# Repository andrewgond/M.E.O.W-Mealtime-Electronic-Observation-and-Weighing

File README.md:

---

# M.E.O.W. — Mealtime Electronic Observation & Weighing (WIP)

**An Open-Source Smart Pet Feeder with Integrated Weight Tracking**
*Senior Design Capstone — Oregon State University*
*Andrew Gondoputro
*Ahmad Alajmi
*Craig Kelley

---

## Project Status: Work in Progress (WIP)

This repository documents the development of the **M.E.O.W. automated pet feeder**, a system that dispenses food and logs pet weight using load cells and RFID identification. The goal is to support long-term tracking of pet health trends such as obesity, malnutrition, or abnormal feeding behavior.

---

# Overview

The M.E.O.W. system is designed to:

* Run on standard wall power
* Measure pet weight within ±20 grams
* Dispense food within ±60 grams
* Log food and weight data within 10 seconds
* Store at least 10 days of logs
* Support up to 4 pets via RFID
* Allow user-configurable feeding parameters

Unlike typical auto-feeders, M.E.O.W. integrates *health-relevant data logging* for improved wellness monitoring.

---

# DEI Commitment

The project emphasizes accessibility, inclusion, and open-source availability.
The system aims to be easy to use for any pet owner, with a simple UI and customizable configuration.

---

# System Architecture

## Top-Level Summary

The system is divided into modular subsystems:

* Power Distribution
* Enclosure & Kinematics
* Sensors
* Code & Database Storage
* Microcontroller (ESP32)
* UI + Web App

---

# 🔌 Block Diagram (Placeholder)

```
[ Block Diagram Placeholder — MEOW System ]
```

```
[ System-Level Diagram Placeholder — Showing Subsystem Connections ]
```

---

# 🔧 Subsystem Descriptions

### 1. Power Distribution

Converts AC wall power into stable low-voltage DC rails for sensors, logic, and actuators.

### 2. Enclosure & Kinematics

Includes the physical enclosure, motors, dispensing components, and protective mechanical structures.

### 3. Sensors

* Load cells to capture weight
* RFID reader for pet identification

### 4. Code & Database

MicroSD-based data storage for logs, timestamps, food dispensing events, and per-pet data.

### 5. Microcontroller

ESP32 manages sensors, actuator control, data logging, and UI communication.

### 6. UI + Web App

Browser-based dashboard for monitoring weight trends, adjusting feeding schedules, and visualizing logs.

---

# Interface Definitions

| Interface           | Description                          |
| ------------------- | ------------------------------------ |
| AC_pwr_in           | Wall power input                     |
| DC_pwr_in_5v        | Regulated 5V power rail              |
| env_weight          | Load cell weight signal              |
| env_rfid_dist       | RFID read distance                   |
| if_user_commands_in | User command interface               |
| motor_ctrl_out      | Motor control signals                |
| ui_disp_ui          | Display output                       |
| db_data_out         | Data sent from database              |
| db_data_to_ui       | Data sent from microcontroller to UI |

---

# Verification Framework

Each subsystem will include:

* Interface validation
* General validation
* Verification steps
* References
* Success criteria

Example tasks include:

* Maximum current draw calculations
* Logic level matching (ESP32 ↔ SD card)
* Regulator thermal margins
* Sensor precision/accuracy tests

---

# References

A `/docs/references.md` file will be added containing:

* Component datasheets
* Industry standards
* Research sources for pet feeding and behavior
* Market analysis references

---

# Future Work

### Technical Recommendations (WIP)

* Improve sensor calibration algorithms
* Add multi-pet discrimination logic
* Enhance UI accessibility
* Expand SD logging features
* Improve enclosure materials

### Teamwork/Communication Recommendations

* Better task delegation strategy
* Implement weekly fixed-scope sprints

---

# Project Roadmap

### Phase 1 — Hardware Bring-Up

* [ ] Power subsystem validation
* [ ] Load cell calibration
* [ ] Servo/stepper testing
* [ ] RFID module bring-up

### Phase 2 — Firmware

* [ ] Sensor polling loops
* [ ] SD logging system
* [ ] Motor control logic
* [ ] Error handling

### Phase 3 — UI + Data

* [ ] Web dashboard
* [ ] Trend graphs
* [ ] Pet profiles

### Phase 4 — Final Integration

* [ ] Full hardware + firmware integration
* [ ] Enclosure finalization
* [ ] Stress testing
* [ ] Final documentation

---

# Contact

Project Contributors:

* Ahmad Alajmi
* Andrew Gondoputro
* Craig Kelley

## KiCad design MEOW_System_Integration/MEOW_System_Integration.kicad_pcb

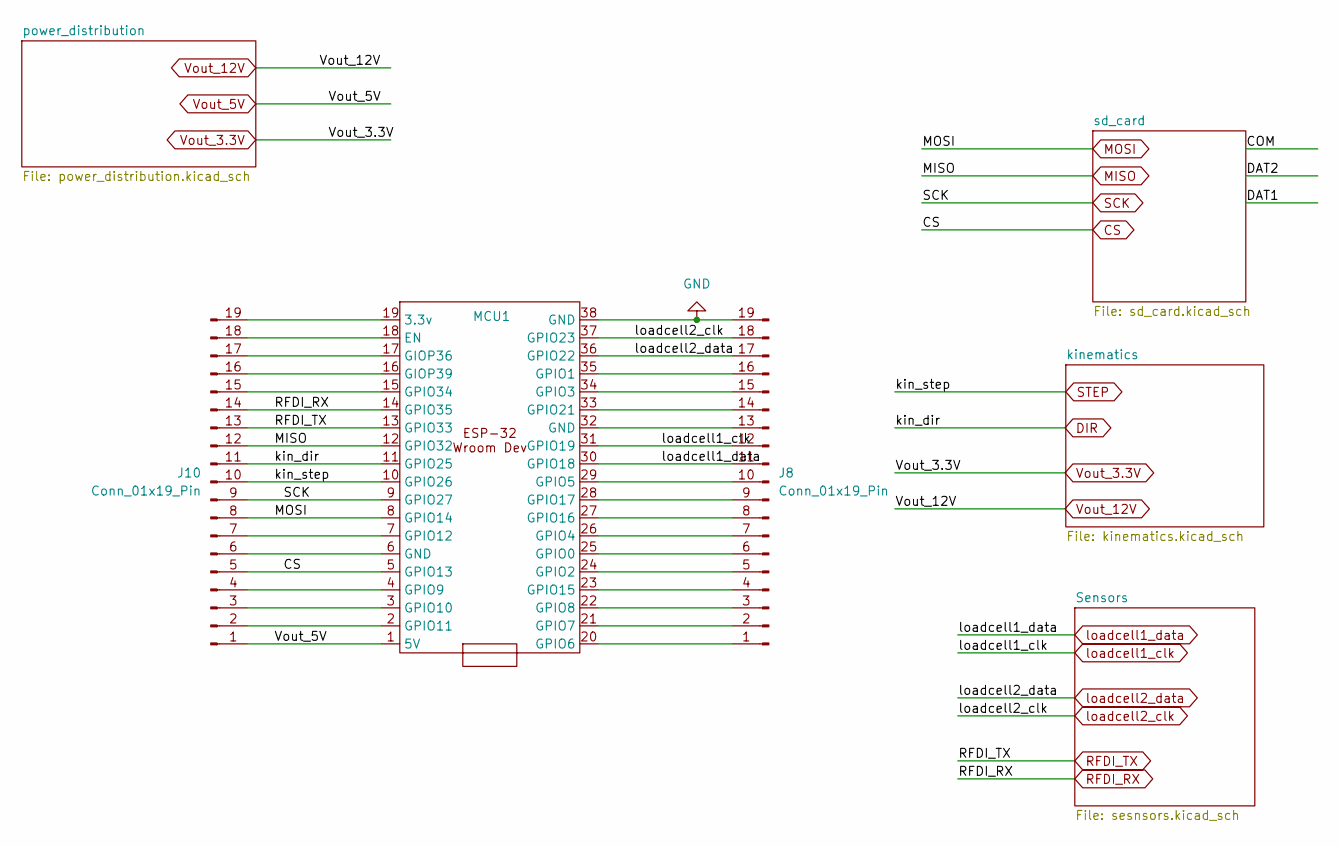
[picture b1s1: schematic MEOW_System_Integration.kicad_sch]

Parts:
J8, J10: Conn_01x19_Pin; PinHeader_1x19_P2.54mm_Vertical
MCU1: ESP32_38pin

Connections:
CS: J10.5, MCU1.5 (GPIO13); also elsewhere on the board
DIR: J10.11, MCU1.11 (GPIO25); also elsewhere on the board
GND: J8.19, MCU1.38 (GND); also elsewhere on the board
MISO: J10.12, MCU1.12 (GPIO32); also elsewhere on the board
MOSI: J10.8, MCU1.8 (GPIO14); also elsewhere on the board
unnamed: J8.1, MCU1.20 (GPIO6)
unnamed: J8.2, MCU1.21 (GPIO7)
unnamed: J8.3, MCU1.22 (GPIO8)
unnamed: J8.4, MCU1.23 (GPIO15)
unnamed: J8.5, MCU1.24 (GPIO2)
unnamed: J8.6, MCU1.25 (GPIO0)
unnamed: J8.7, MCU1.26 (GPIO4)
unnamed: J8.8, MCU1.27 (GPIO16)
unnamed: J8.9, MCU1.28 (GPIO17)
unnamed: J8.10, MCU1.29 (GPIO5)
unnamed: J8.13, MCU1.32 (GND)
unnamed: J8.14, MCU1.33 (GPIO21)
unnamed: J8.15, MCU1.34 (GPIO3)
unnamed: J8.16, MCU1.35 (GPIO1)
unnamed: J10.2, MCU1.2 (GPIO11)
unnamed: J10.3, MCU1.3 (GPIO10)
unnamed: J10.4, MCU1.4 (GPIO9)
unnamed: J10.6, MCU1.6 (GND)
unnamed: J10.7, MCU1.7 (GPIO12)
unnamed: J10.15, MCU1.15 (GPIO34)
unnamed: J10.16, MCU1.16 (GIOP39)
unnamed: J10.17, MCU1.17 (GIOP36)
unnamed: J10.18, MCU1.18 (EN)
unnamed: J10.19, MCU1.19 (3.3v)
RFDI_RX: J10.14, MCU1.14 (GPIO35); also elsewhere on the board
RFDI_TX: J10.13, MCU1.13 (GPIO33); also elsewhere on the board
SCK: J10.9, MCU1.9 (GPIO27); also elsewhere on the board
STEP: J10.10, MCU1.10 (GPIO26); also elsewhere on the board
Vout_5V: J10.1, MCU1.1 (5V); also elsewhere on the board
loadcell1_clk: J8.12, MCU1.31 (GPIO19); also elsewhere on the board
loadcell1_data: J8.11, MCU1.30 (GPIO18); also elsewhere on the board
loadcell2_clk: J8.18, MCU1.37 (GPIO23); also elsewhere on the board
loadcell2_data: J8.17, MCU1.36 (GPIO22); also elsewhere on the board

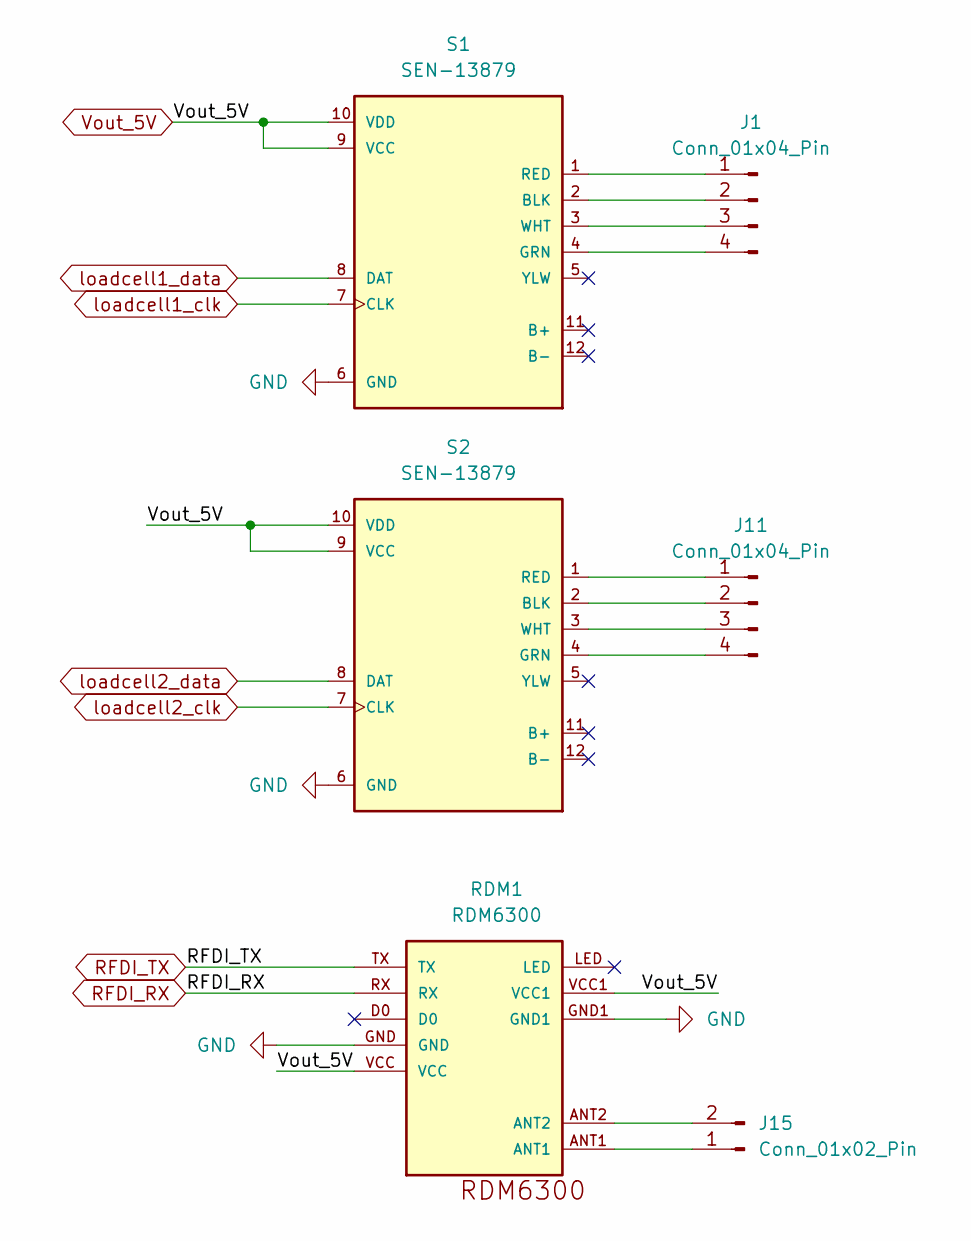
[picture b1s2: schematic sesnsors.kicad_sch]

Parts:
J1, J11: Conn_01x04_Pin; PinHeader_1x04_P2.54mm_Vertical
J15: Conn_01x02_Pin; PinSocket_1x02_P2.54mm_Vertical
RDM1: RDM6300
S1, S2: SEN-13879; SPARKFUN_SEN-13879

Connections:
GND: RDM1.GND, RDM1.GND1, S1.6 (GND), S2.6 (GND); also elsewhere on the board
unnamed: J1.1, S1.1 (RED)
unnamed: J1.2, S1.2 (BLK)
unnamed: J1.3, S1.3 (WHT)
unnamed: J1.4, S1.4 (GRN)
unnamed: J11.1, S2.1 (RED)
unnamed: J11.2, S2.2 (BLK)
unnamed: J11.3, S2.3 (WHT)
unnamed: J11.4, S2.4 (GRN)
unnamed: J15.1, RDM1.ANT1
unnamed: J15.2, RDM1.ANT2
RFDI_RX: RDM1.RX; also elsewhere on the board
RFDI_TX: RDM1.TX; also elsewhere on the board
Vout_5V: RDM1.VCC, RDM1.VCC1, S1.9 (VCC), S1.10 (VDD), S2.9 (VCC), S2.10 (VDD); also elsewhere on the board
loadcell1_clk: S1.7 (CLK); also elsewhere on the board
loadcell1_data: S1.8 (DAT); also elsewhere on the board
loadcell2_clk: S2.7 (CLK); also elsewhere on the board
loadcell2_data: S2.8 (DAT); also elsewhere on the board

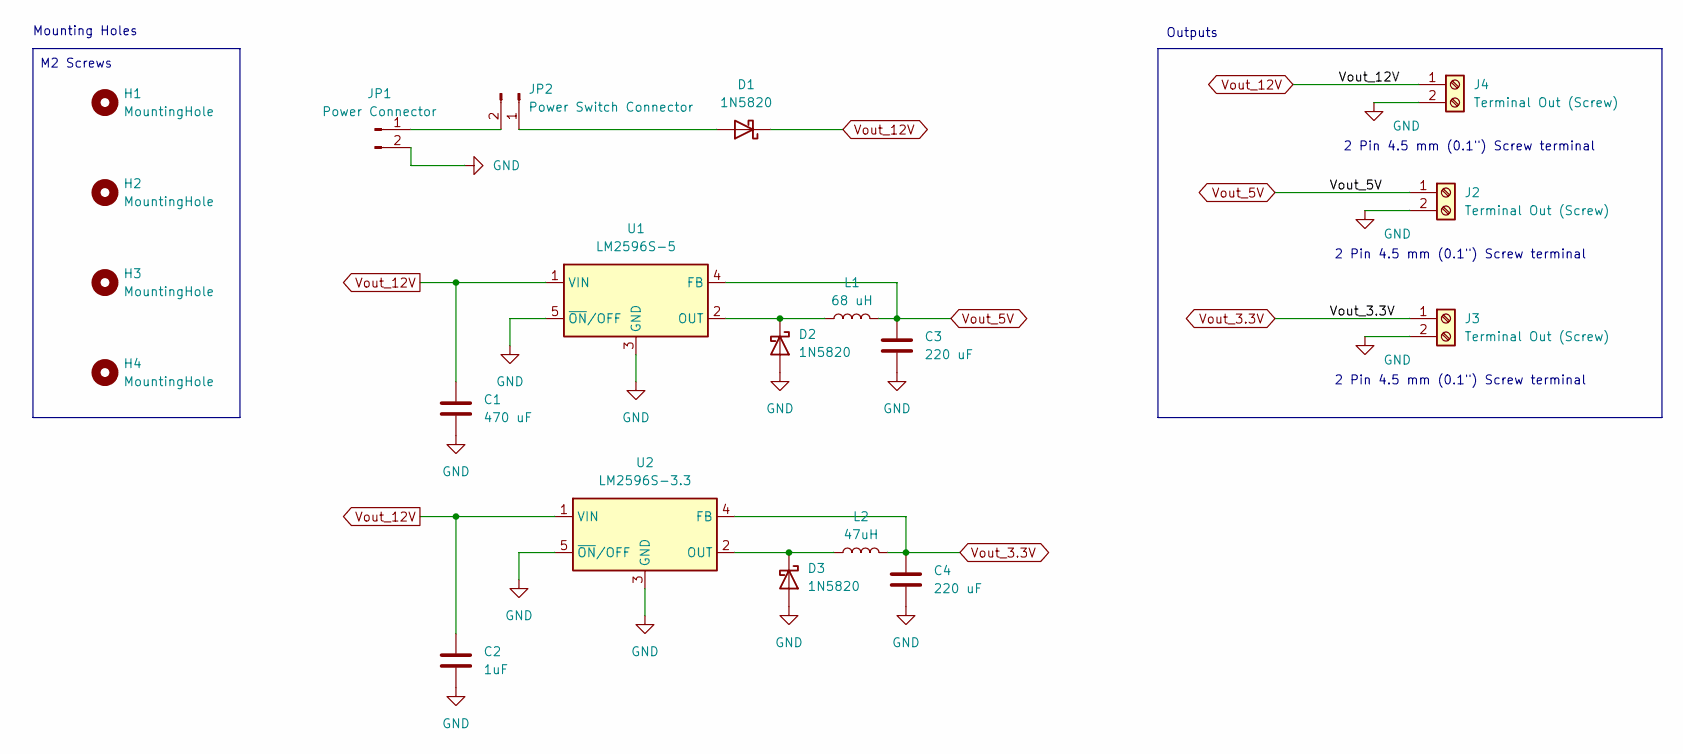
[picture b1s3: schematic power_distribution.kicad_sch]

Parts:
C1: 470 uF; CP_Elec_8x10
C2: 1uF; C_0603_1608Metric
C3, C4: 220 uF; CP_Elec_6.3x7.7
D1, D2, D3: 1N5820; D_SMA
H1, H2, H3, H4: MountingHole; MountingHole_3mm
J2, J3, J4: Terminal Out (Screw); TerminalBlock_TE_282834-2_1x02_P2.54mm_Horizontal
JP1: Power Connector; JST_EH_B2B-EH-A_1x02_P2.50mm_Vertical
JP2: Power Switch Connector; JST_EH_B2B-EH-A_1x02_P2.50mm_Vertical
L1: 68 uH; L_12x12mm_H4.5mm
L2: 47uH; L_12x12mm_H4.5mm
U1: LM2596S-5; TO-263-5_TabPin3
U2: LM2596S-3.3; TO-263-5_TabPin3

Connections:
GND: C1.2, C2.2, C3.2, C4.2, D2.2 (A), D3.2 (A), JP1.2, U1.3 (GND), U1.5 (~ON/OFF), U2.3 (GND), U2.5 (~ON/OFF); also elsewhere on the board
unnamed: D1.2 (A), JP2.1
unnamed: D2.1 (K), L1.1, U1.2 (OUT)
unnamed: D3.1 (K), L2.1, U2.2 (OUT)
unnamed: JP1.1, JP2.2
Vout_3.3V: C4.1, L2.2, U2.4 (FB); also elsewhere on the board
Vout_5V: C3.1, L1.2, U1.4 (FB); also elsewhere on the board
Vout_12V: C1.1, C2.1, D1.1 (K), U1.1 (VIN), U2.1 (VIN); also elsewhere on the board

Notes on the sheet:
Outputs
2 Pin 4.5 mm (0.1") Screw terminal
Mounting Holes
M2 Screws

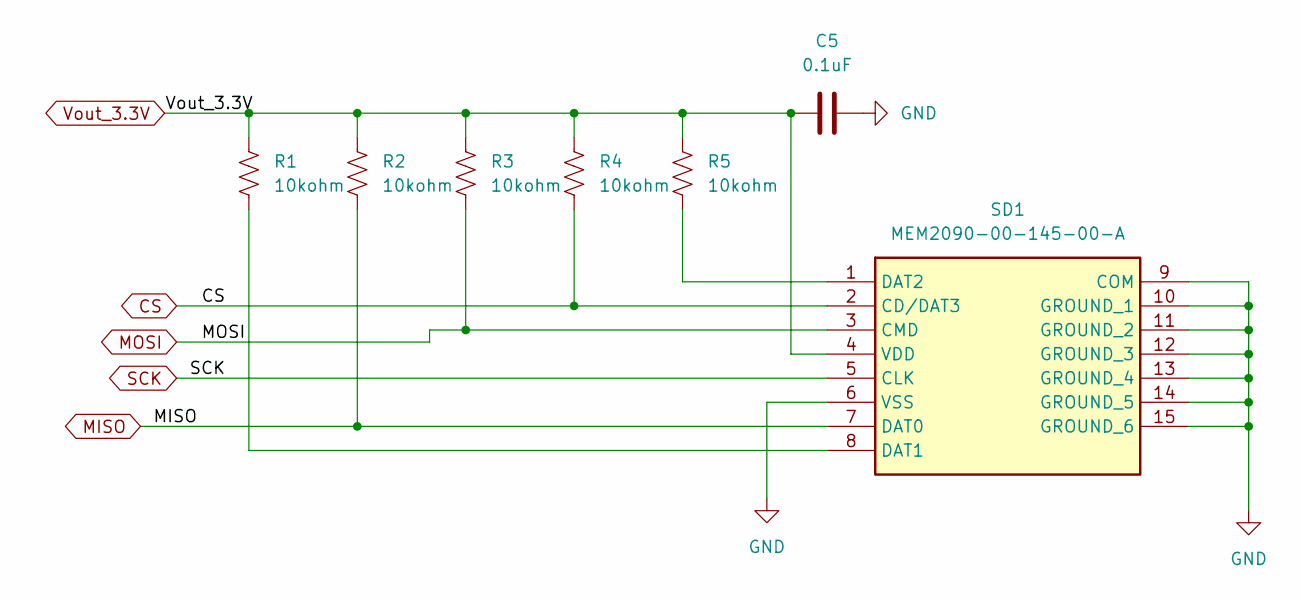
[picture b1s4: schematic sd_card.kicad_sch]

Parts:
C5: 0.1uF; C_0603_1608Metric
R1, R2, R3, R4, R5: 10kohm; R_0603_1608Metric_Pad0.98x0.95mm_HandSolder
SD1: MEM2090-00-145-00-A; MEM20900014500A; Mouser Part Number 640-MEM20900014500A

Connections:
CS: R4.2, SD1.2 (CD/DAT3); also elsewhere on the board
GND: C5.2, SD1.6 (VSS), SD1.9 (COM), SD1.10 (GROUND_1), SD1.11 (GROUND_2), SD1.12 (GROUND_3), SD1.13 (GROUND_4), SD1.14 (GROUND_5), SD1.15 (GROUND_6); also elsewhere on the board
MISO: R2.2, SD1.7 (DAT0); also elsewhere on the board
MOSI: R3.2, SD1.3 (CMD); also elsewhere on the board
unnamed: R1.2, SD1.8 (DAT1)
unnamed: R5.2, SD1.1 (DAT2)
SCK: SD1.5 (CLK); also elsewhere on the board
Vout_3.3V: C5.1, R1.1, R2.1, R3.1, R4.1, R5.1, SD1.4 (VDD); also elsewhere on the board

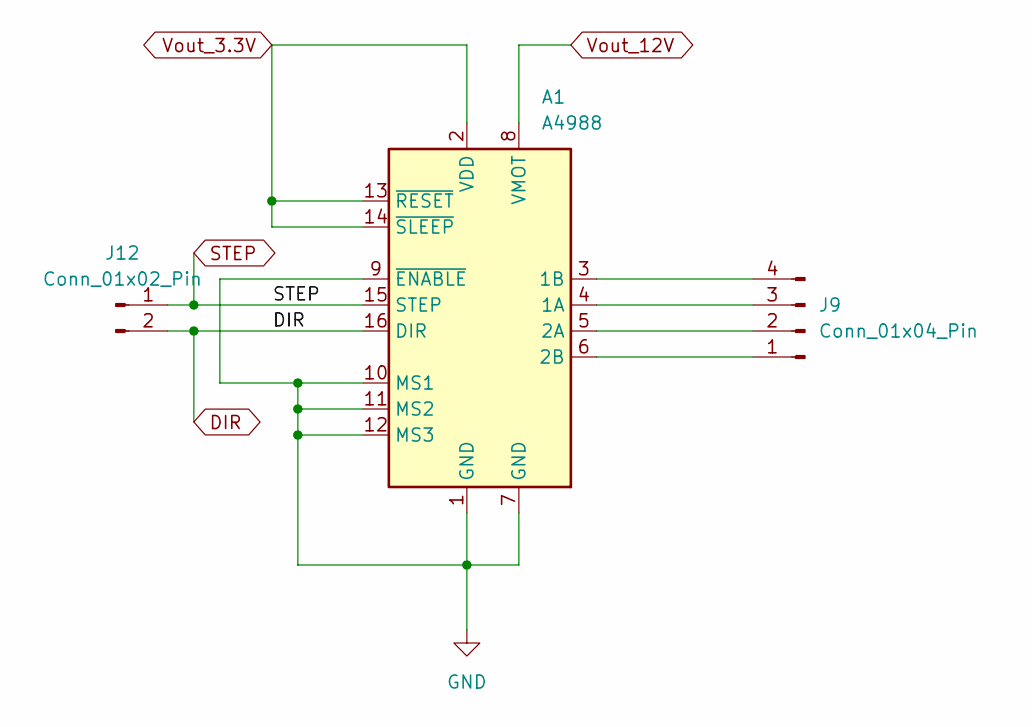
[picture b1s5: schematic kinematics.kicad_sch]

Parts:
A1: A4988; Pololu_Breakout-16_15.2x20.3mm
J9: Conn_01x04_Pin; PinSocket_1x04_P2.54mm_Vertical
J12: Conn_01x02_Pin; PinSocket_1x02_P2.54mm_Vertical

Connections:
DIR: A1.16 (DIR), J12.2; also elsewhere on the board
GND: A1.1 (GND), A1.7 (GND), A1.9 (~ENABLE), A1.10 (MS1), A1.11 (MS2), A1.12 (MS3); also elsewhere on the board
unnamed: A1.4 (1A), J9.3
unnamed: A1.3 (1B), J9.4
unnamed: A1.5 (2A), J9.2
unnamed: A1.6 (2B), J9.1
STEP: A1.15 (STEP), J12.1; also elsewhere on the board
Vout_3.3V: A1.2 (VDD), A1.13 (~RESET), A1.14 (~SLEEP); also elsewhere on the board
Vout_12V: A1.8 (VMOT); also elsewhere on the board

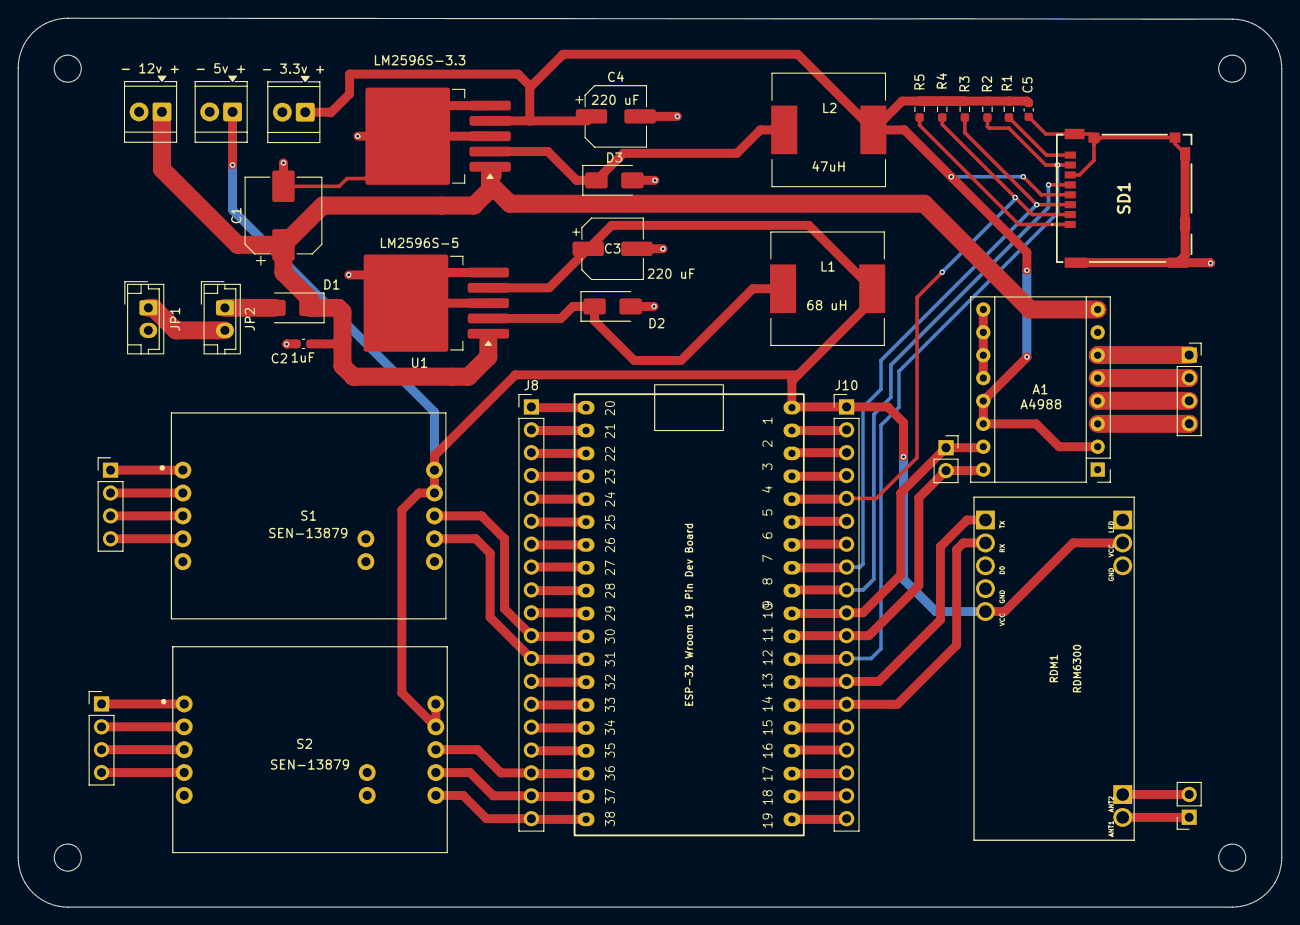
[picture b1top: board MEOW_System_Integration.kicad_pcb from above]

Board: 2 copper layers, 140.3 x 98.7 mm, 39 parts (0 on the bottom side), 60 nets.

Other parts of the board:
- 3.3v +, - 5v +, - 12v +: Terminal Out (Screw); TerminalBlock_TE_282834-2_1x02_P2.54mm_Horizontal

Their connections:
GND: - 3.3v +.2, - 5v +.2, - 12v +.2; also elsewhere on the board
Vout_3.3V: - 3.3v +.1; also elsewhere on the board
Vout_5V: - 5v +.1; also elsewhere on the board
Vout_12V: - 12v +.1; also elsewhere on the board

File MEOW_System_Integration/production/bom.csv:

Designator,Footprint,Quantity,Value,LCSC Part #
"- 12V +, - 3.3V +, - 5V +",TerminalBlock_TE_282834-2_1x02_P2.54mm_Horizontal,3,Terminal Out (Screw),
A1,Pololu_Breakout-16_15.2x20.3mm,1,A4988,
C1,CP_Elec_8x10,1,470 uF,
C2,0603,1,1uF,
"C3, C4",CP_Elec_6.3x7.7,2,220 uF,
C5,0603,1,0.1uF,
"D1, D2, D3",D_SMA,3,1N5820,
"J1, J11",PinHeader_1x04_P2.54mm_Vertical,2,Conn_01x04_Pin,
"J10, J8",PinHeader_1x19_P2.54mm_Vertical,2,Conn_01x19_Pin,
"J12, J15",PinSocket_1x02_P2.54mm_Vertical,2,Conn_01x02_Pin,
J9,PinSocket_1x04_P2.54mm_Vertical,1,Conn_01x04_Pin,
JP1,JST_EH_B2B-EH-A_1x02_P2.50mm_Vertical,1,Power Connector,
JP2,JST_EH_B2B-EH-A_1x02_P2.50mm_Vertical,1,Power Switch Connector,
L1,L_12x12mm_H4.5mm,1,68 uH,
L2,L_12x12mm_H4.5mm,1,47uH,
MCU1,ESP32_38pin,1,~,
"R1, R2, R3, R4, R5",0603,5,10kohm,
RDM1,RDM6300,1,RDM6300,
"S1, S2",SPARKFUN_SEN-13879,2,SEN-13879,
SD1,MEM20900014500A,1,MEM2090-00-145-00-A,
U1,TO-263-5_TabPin3,1,LM2596S-5,
U2,TO-263-5_TabPin3,1,LM2596S-3.3,

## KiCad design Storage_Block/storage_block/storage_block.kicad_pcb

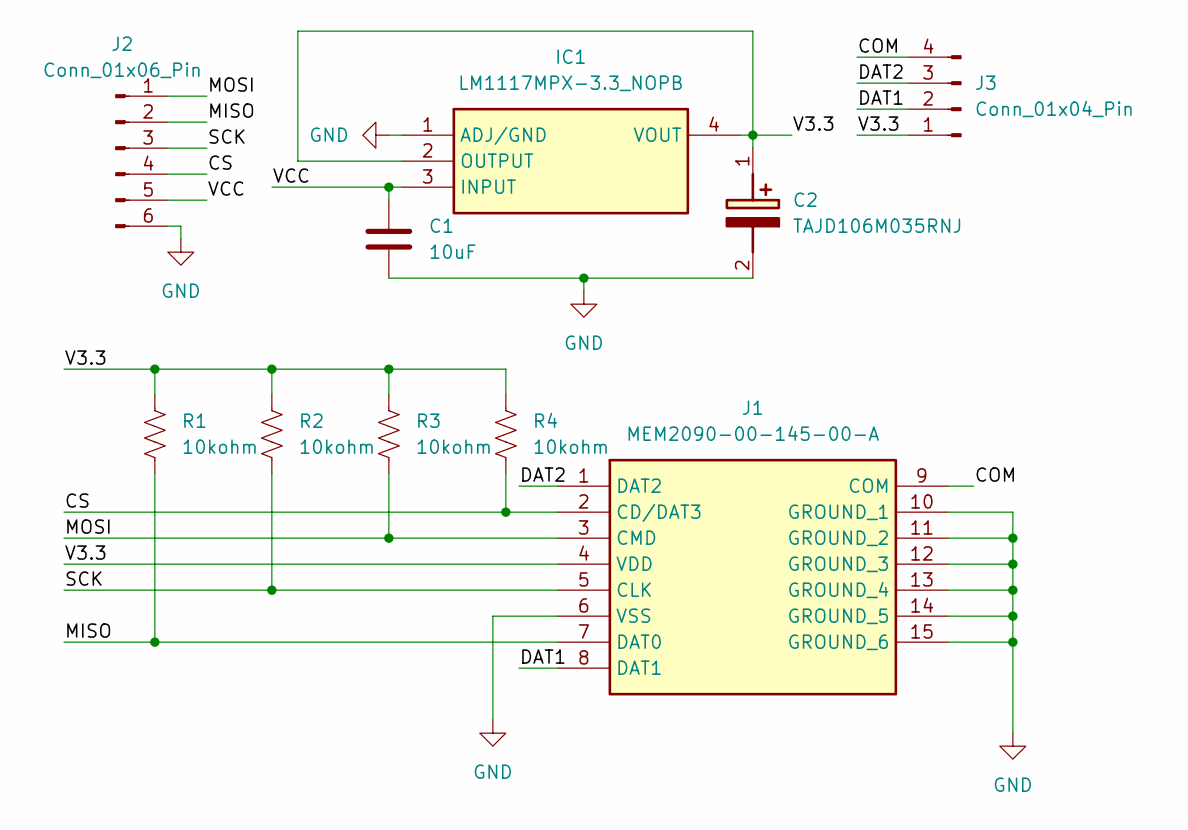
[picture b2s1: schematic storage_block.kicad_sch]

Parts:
C1: 10uF; C_1206_3216Metric_Pad1.33x1.80mm_HandSolder
C2: TAJD106M035RNJ; CAPPM7344X310N; Mouser Part Number 581-TAJD106M035R
IC1: LM1117MPX-3.3_NOPB; SOT230P700X180-4N; Mouser Part Number 926-LM1117MPX3.3NOPB
J1: MEM2090-00-145-00-A; MEM20900014500A; Mouser Part Number 640-MEM20900014500A
J2: Conn_01x06_Pin; PinHeader_1x06_P2.54mm_Vertical
J3: Conn_01x04_Pin; PinHeader_1x04_P2.54mm_Vertical
R1, R2, R3, R4: 10kohm; R_0603_1608Metric_Pad0.98x0.95mm_HandSolder

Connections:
/COM: J1.9 (COM), J3.4
/CS: J1.2 (CD/DAT3), J2.4, R4.2
/DAT1: J1.8 (DAT1), J3.2
/DAT2: J1.1 (DAT2), J3.3
/MISO: J1.7 (DAT0), J2.2, R1.2
/MOSI: J1.3 (CMD), J2.1, R3.2
/SCK: J1.5 (CLK), J2.3, R2.2
/V3.3: C2.1 (+), IC1.2 (OUTPUT), IC1.4 (VOUT), J1.4 (VDD), J3.1, R1.1, R2.1, R3.1, R4.1
/VCC: C1.2, IC1.3 (INPUT), J2.5
GND: C1.1, C2.2 (-), IC1.1 (ADJ/GND), J1.6 (VSS), J1.10 (GROUND_1), J1.11 (GROUND_2), J1.12 (GROUND_3), J1.13 (GROUND_4), J1.14 (GROUND_5), J1.15 (GROUND_6), J2.6

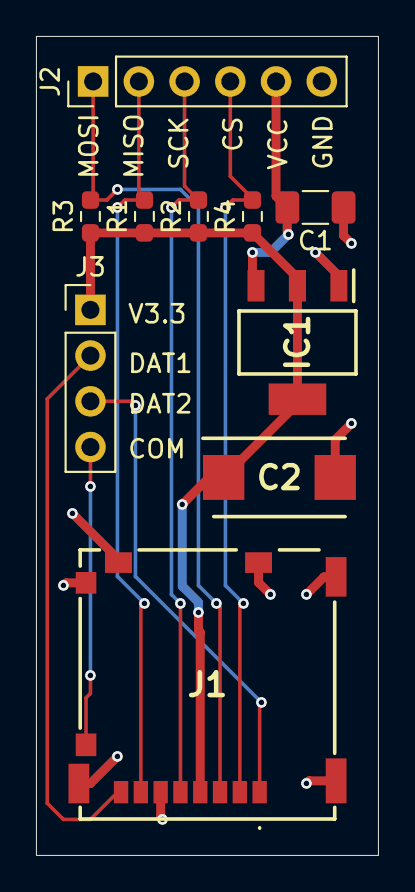
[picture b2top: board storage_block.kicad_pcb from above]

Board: 2 copper layers, 19.0 x 45.5 mm, 10 parts (0 on the bottom side), 10 nets.

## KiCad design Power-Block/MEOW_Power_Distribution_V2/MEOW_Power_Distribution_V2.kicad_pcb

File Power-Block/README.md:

#1.1. Power Block - Andrew Gondoputro

This block is located on the exterior input of the system, accepting standard U.S. wall power and converting it into a regulated low-voltage DC bus at several predetermined voltages that all other M.E.O.W. subsystems can utilize. Every other block in the system depends on this stable power for its parts to function and is in charge of isolation, overcurrent protection, and providing enough power for the other components in the system.

#1.1.1. Description

The Power Distribution Block takes the AC_pwr_in interface with the US Standard 120 VAC, 60 Hz from a U.S. wall outlet. This allows us to plug into a wall and have a consistent power source, unlike a battery. Internally, the block then takes this AC wall power and turns it into a 12V rail, for higher voltage operations on the system like the kinematics of moving the stepper motors. It then uses that 12V rail to step down into both a 5V rail and a 3.3V rail, used for lower voltage components like the microcontroller, stepper drivers and sensors.

#1.1.2. Design

The design of the power station first starts with connecting to a wall outlet. Standard NEMA US Connectors consist of two pinned enclosures. We decided to have the cleanest AC->DC conversion to use a purchasable wall mount 12V 2A adapter with a barrel jack connector [10]. This also allows the cable of our overall system to be modular in which you can disconnect from the system and also easily replace.

Starting our circuit, we designed a barrel jack connector as an input for just a power and gnd, making sure that the footprint was right on the schematic. From the power pin A we put a Schmitt trigger diode so we would not get any accidental reverse current. The next node from the diode would just be used as the 12 V rail for the system since it was already cleaned by the adapter.

We decided to use two-buck conversions for the least amount of heat problems. We went with the LM2596S because of its easy accessibility of purchasing and consistent documentation and usages. The system then uses a 470uF and 1uF capacitor to deal with any low/high frequency noise. Our system uses two LM2596S taking the 12V input, with one LM2596S downstepping to 5V and the other downstepping to 3.3V. Following the example of [3, pg 1] we looked for capacitors and inductors and the wiring of the buck converters. Tables 9.1 and 9.3 [3, pg 21] showed us which inductors and capacitors to use. Which can be seen in our schematic [Figure 3.1.1]. The outputs of the buck converters gave us our rails we would be using.

Moving onto our PCB we that we decided that our project would later become open source, we tried to use a lot of through-hole components for easier assembly. We spent a long time looking for footprints and then making 1.5mm traces for high-power components. The pcb layout ended up being about the size of a credit card and can be seen in Figure 3.1.2. We then used screw terminals for the outputs of the rails for testing purposes when creating the PCB.

#Design Artifacts

Figure 3.1.1 KiCAD Schematic
Figure 3.1.2 KiCAD PCB Trace Schematic
Figure 3.1.2 KiCAD PCB 3D Model

#1.1.3. General Validation

It uses an AC to DC 12V power adapter to get the first regulated rail. It then uses a DC Voltage regulator to convert that 12V DC to a single 5 V DC regulated output that is used by the other blocks. Internally, this 5V is then fed into another voltage regulator to get a single 3.3 V DC regulated output for a microcontroller. This design aligns with the top-level system plan, which calls out a dedicated power block alongside enclosure/kinematics, sensors, microcontroller, code/database, and UI.

#1.1.4. Interface Validation

Interface property
Be sure to use the naming convention “from_to_type” here.
Why is this interface property this value?
How do you know your design details will meet or exceed this property? Cite your sources in IEEE.

**Interface 1: ext_power_acpwr**
| Interface property                                 | Why is this interface property this value?                                                                       | How do you know your design details will meet or exceed this property?                                                   |
| -------------------------------------------------- | ---------------------------------------------------------------------------------------------------------------- | ------------------------------------------------------------------------------------------------------------------------ |
| **V_rms = 120 VAC @ 60 Hz (wall_pwr_pwr_ac)**      | Section 1 and 2 say “The system will use standard US wall.” U.S. residential mains are 120 VAC nominal at 60 Hz. | The selected AC-DC module is rated for 90–132 VAC input at 47–63 Hz, so 120 VAC/60 Hz is inside range. [10]              |
| **I_in_max ≤ 0.5 A (wall_pwr_pwr_ac)**             | A 15 W / 5 V / 3 A supply at 120 VAC draws ~0.17 A even at poor PF.                                              | Adapter rating guarantees operation below this current. [10]                                                             |
| **Connector = 2-pin shielded / enclosure mounted** | Since we take wall power, this is the easiest AC→DC form factor.                                                 | Using an IEC/2-pin inlet with strain relief meets electrical and mechanical requirements; it is also the purchased part. |
| **Barrel Connector Between PCB and Outlet**        | Typical devices use a separate connector so the cord is removable.                                               | 2.1 mm male/female barrel jacks are used. [10]                                                                           |

**Interface 2. power_enc_dcpwr12v**
| Interface property                 | Why is this interface property this value?                                    | How do you know your design meets this property?                                |
| ---------------------------------- | ----------------------------------------------------------------------------- | ------------------------------------------------------------------------------- |
| **V_min = 11.1 V (pwr_all_dcpwr)** | 12 V ±7.5% allows the buck converter and stepper motors to operate correctly. | Stepper motor is rated 8–35 V, well within range. [7]                           |
| **V_max = 12.9 V (pwr_all_dcpwr)** | Same tolerance requirement as above.                                          | Stepper motor and converters operate fully across this range. [7]               |
| **I_nom = 250 mA**                 | Expected slow-movement draw of the motor.                                     | LM2596S converter maintains regulation at no load and normal load. [3]          |
| **I_peak = 300 mA**                | Ensures startup + acceleration overhead is supported.                         | Stepper motors typically require ≤ 300 mA under these operating conditions. [7] |

**Interface 3. dc_pwr_out_5v**

| Interface property     | Why is this interface property this value?                  | How do you know your design meets/exceeds it?                                        |
| ---------------------- | ----------------------------------------------------------- | ------------------------------------------------------------------------------------ |
| **V_min = 4.625 V**    | 5 V −7.5% is USB and logic lower tolerance limit.           | LM2596S guarantees ±10% output; verified by open-circuit tests. [3]                  |
| **V_max = 5.375 V**    | 5 V +7.5% keeps downstream devices safe.                    | LM2596S ±5% accuracy meets this requirement.                                         |
| **I_nominal = 100 mA** | Matches typical load cells and sensor current requirements. | ESP32 quiescent current = 5 mA; total expected load = 105 mA < nominal limit. [2][6] |
| **I_peak = 300 mA**    | Supports transient demands.                                 | Load remains below converter limit; ESP32 remains far under this threshold.          |

Interface 4. dc_pwr_out_3.3v
| Interface property             | Why is this interface property this value?                | How do you know your design meets/exceeds it?                       |
| ------------------------------ | --------------------------------------------------------- | ------------------------------------------------------------------- |
| **V_min = 3.0525 V**           | 3.3 V −7.5% meets logic tolerance for ESP32/sensors.      | LM2596S regulation ensures output stays above this even under load. |
| **V_max = 3.5475 V**           | 3.3 V +7.5% stays within max voltage for logic chips.     | Verified by open-circuit measurement ≤ 3.465 V. [3]                 |
| **I_nominal = 100 mA ± 25 mA** | Normal operating range for microcontroller + peripherals. | ESP32 quiescent is 5 mA; typical load ≤ 105 mA.                     |
| **I_peak = 300 mA**            | Allows for transient inrush conditions.                   | Remains well below LM2596S converter limits.                        |

#1.1.5. Verification Process
Interface 1: ext_power_acpwr

Barrel Jack Connector and 2-pin shielded connector

Connect the cable to the system’s PCB barrel jack connector

Plug the system’s wall connector into the wall
VRMS (NEMA Standard) and Iinmax (Wall Adapter)

Use a multimeter on the rails to check the voltage of each rail receiving their expected values

Fully verify the interfaces 2-4 validation’s to ensure its working'

Interface 2: power_enc_dcpwr12v

11.1V < Vout < 12.9V and Imin= 0 (Verifying when motor off)

Disconnect any loads on the 12V rail

While the system is connected to wall power, use a multimeter to verify that the values are within the range

11.4V < Vout < 12.6V when Imax= 250 mA (Verifying when motor on)
3. Have the system disconnected from the wall
4. Put the electronic load on the 12V rail with power and gnd properly wired
a. Set the load to I = 0.3 and then turn it on
b. Put a resistor value of 22 ohms on the 5V Rail (Simulating I = 227mA)
c. resistor value of 22 ohms on the 3V Rail (Simulating I = 150mA)
5. Plug the system into the wall
6. Check the electronic load to see the actual current and the voltage across the node to verify its within the values

11.4V < Vout < 12.6V when Imax = 300 mA (Verifying under max load range)

Unplug the system

Change electronic load to I=0.3

Plug the system back into the wall

Check the electronic load to see the actual current and the voltage across the node to verify its within the values

Interface 3: power_sensors_dcpwr5v

4.625 V < Vout < 5.375 V
5. Disconnect any loads on the 5V rail
6. While the system is connected to wall power, use a multimeter to verify that the values are within the range

4.625 V < Vout < 5.375 V when Inom = 200 mA (Verifying under nominal load range)
7. Have the system disconnected from the wall
8. Put the electronic load on the 12V rail with power and gnd properly wired
a. Set the load to I = 0.1 and then turn it on
b. Put a resistor value of 47 ohms on the 12V Rail (Simulating I = 255mA)
c. resistor value of 22 ohms on the 3V Rail (Simulating I = 150mA)
9. Plug the system into the wall
10. Check the electronic load to see the actual current and the voltage across the node to verify its within the values

4.625 V < Vout < 5.375 V when Imax = 300 mA (Verifying under max load range)
11. Unplug the system
12. Change electronic load to I=0.3
13. Plug the system back into the wall
14. Check the electronic load to see the actual current and the voltage across the node to verify its within the values

Interface 4: power_enc_dcpwr3.3v

3.05 V < Vout < 3.55 V (Verifying when system idle)

Disconnect any loads on the 12V rail

While the system is connected to wall power, use a multimeter to verify that the values are within the range

3.05 V < Vout < 3.55 V when Inom = 200 mA (Verifying under nominal load range)
3. Have the system disconnected from the wall
4. Put the electronic load on the 12V rail with power and gnd properly wired
a. Set the load to I = 0.1 and then turn it on
b. Put a resistor value of 47 ohms on the 12V Rail (Simulating I = 255mA)
c. resistor value of 22 ohms on the 5V Rail (Simulating I = 227mA)
5. Plug the system into the wall
6. Check the electronic load to see the actual current and the voltage across the node to verify its within the values

3.05 V < Vout < 3.55 V when Imax = 300 mA (Verifying under max load range)
7. Unplug the system
8. Change electronic load to I=0.3
9. Plug the system back into the wall
10. Check the electronic load to see the actual current and the voltage across the node to verify its within the values

1.1.6. References

(All references preserved exactly from the PDF)

[1] Americord Custom Power Cords, “NEMA Chart: Know Your Plug And Receptacle,” Americord Blog, Jul. 24, 2021.
[2] ON Semiconductor, “NCP1117/D: 1.0 A Low-Dropout Positive Fixed and Adjustable Voltage Regulators.”
[3] Texas Instruments / LM2596S Evaluation Module, “LM2596S EV Board Datasheet,” Digi-Key, 2020.
[4] Cliff Electronic Components Ltd., “Model No. DC-10A / DC-10B – Part No. FC68148.”
[5] Espressif Systems, “ESP32-WROOM-32 Datasheet.”
[6] SparkFun Electronics, “ESP32 Datasheet (Alternate Copy).”
[7] Allegro MicroSystems, “A4988: Microstepping Motor Driver with Translator.”
[8] Rubycon Corp., “YXJ Series Aluminum Electrolytic Capacitors.”
[9] Rubycon Corp., “ZLH Series Aluminum Electrolytic Capacitors.”
[10] Yageo Group, “12V 2A Power Supply.”
[11] Vishay Semiconductors, “1N5820 Schottky Barrier Rectifier.”
[12] Würth Elektronik, “744731680 – WE-PD Series Shielded Power Inductor.”
[13] Würth Elektronik, “7447471470 – WE-HCI Series High-Current Inductor.”
[14] Texas Instruments, “LM2596: SIMPLE SWITCHER® 150-kHz 3-A Step-Down Voltage Regulator.”

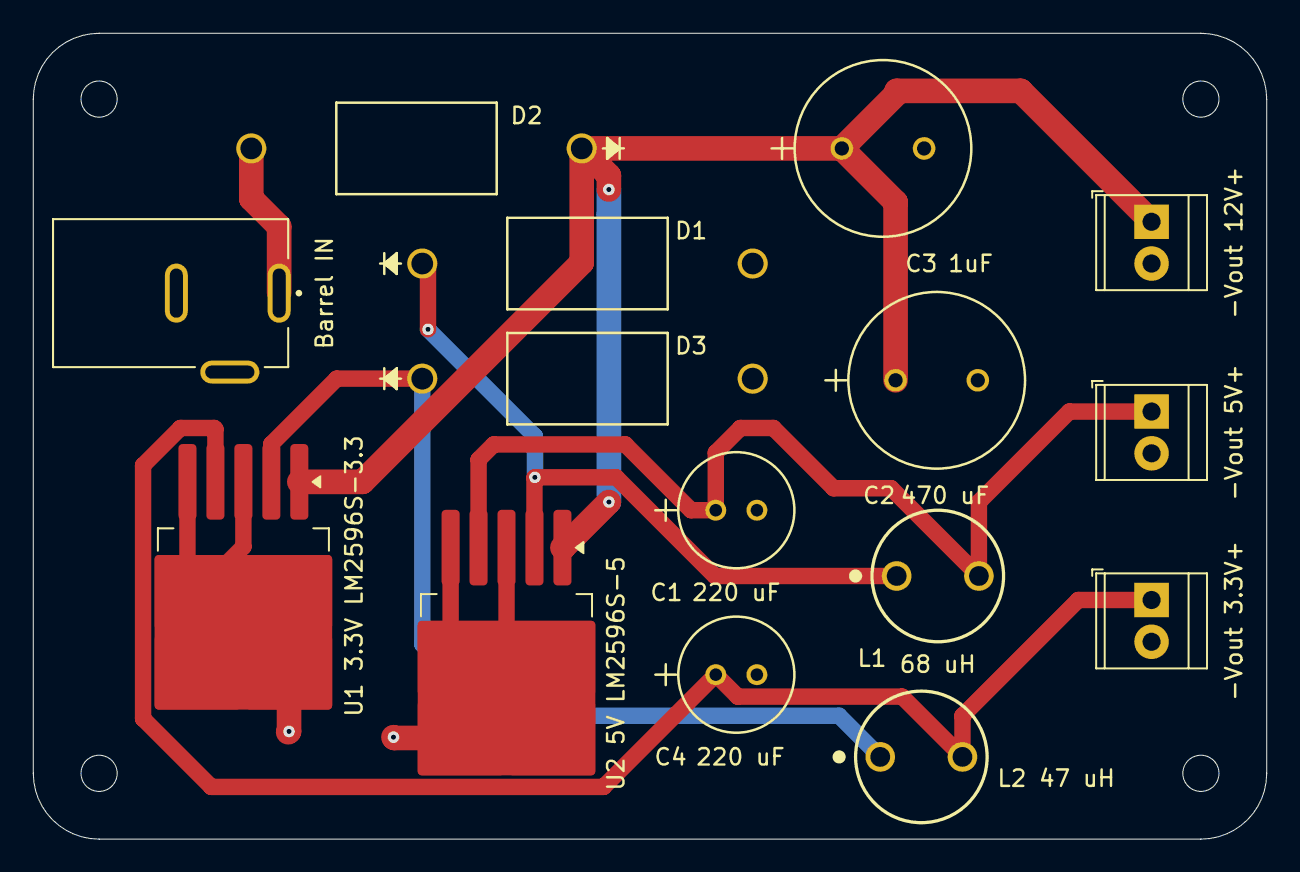
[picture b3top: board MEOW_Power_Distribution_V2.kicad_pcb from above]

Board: 2 copper layers, 75.0 x 49.0 mm, 19 parts (0 on the bottom side), 7 nets.

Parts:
Barrel IN: 54-00166; TENSILITY_54-00166
C1, C4: 220 uF; CAP_YX_6P3X11_RUB
C2: 470 uF; CAP_YX_10X12P5_RUB
C3: 1uF; CAP_YX_10X12P5_RUB
D1, D2, D3: 1N5820; CR_0-E3&slash_54_VIS
H1, H2, H3, H4: MountingHole; MountingHole_2.2mm_M2
J3, J4, J6: Terminal Out (Screw); TerminalBlock_TE_282834-2_1x02_P2.54mm_Horizontal
L1: 68 uH; WE-TIS_8075
L2 47 uH: 47uH; WE-TIS_8075
U1 3.3V LM2596S-3.3: LM2596S-3.3; TO-263-5_TabPin3
U2 5V LM2596S-5: LM2596S-5; TO-263-5_TabPin3

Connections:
GND: Barrel IN.B, C1.2, C2.2, C3.2, C4.2, D1.2 (A), D3.2 (A), J3.2, J4.2, J6.2, U1 3.3V LM2596S-3.3.3 (GND), U1 3.3V LM2596S-3.3.5 (~ON/OFF), U2 5V LM2596S-5.3 (GND), U2 5V LM2596S-5.5 (~ON/OFF)
unnamed: D1.1 (K), L1.1, U2 5V LM2596S-5.2 (OUT)
unnamed: Barrel IN.A, D2.2 (A)
unnamed: D3.1 (K), L2 47 uH.1, U1 3.3V LM2596S-3.3.2 (OUT)
Vout_3.3V: C4.1, J6.1, L2 47 uH.2, U1 3.3V LM2596S-3.3.4 (FB)
Vout_5V: C1.1, J4.1, L1.2, U2 5V LM2596S-5.4 (FB)
Vout_12V: C2.1, C3.1, D2.1 (K), J3.1, U1 3.3V LM2596S-3.3.1 (VIN), U2 5V LM2596S-5.1 (VIN)

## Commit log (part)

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2025-11-26 Revise README for M.E.O.W. project details
    Updated the README to provide detailed project information for M.E.O.W., an automated pet feeder with integrated weight tracking. Included sections on project status, system architecture, subsystem d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
2025-11-26 Standardize section headers in README.md
    Updated section headers in README.md for consistency.
2025-12-05 added storage block kicad files and test code
2025-12-07 Revise README for Power Block clarity and detail
    Updated the README to provide a clearer overview of the Power Block's functionality and design, including details on power conversion, rail specifications, and validation processes.
2025-12-07 Refactor README.md for improved structure
    Updated formatting in README.md for better readability and structure, including section headings and interface descriptions.
2026-01-31 Added A system intergration schematic
2026-02-06 Updated System as much as possible
2026-02-17 Added Physical Enclsoure files
2026-02-18 simple sensor block kicad
2026-04-03 current status PCB ordered
2026-05-05 Add link to Thingiverse designs in README
2026-05-06 Fix typo in contributor's name
2026-05-07 initial system code
2026-05-07 updated cad stuff
2026-05-07 Updated with Ahmad's stuff
